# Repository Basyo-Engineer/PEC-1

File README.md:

# PEC-1
Hand made 8bitCPU, Prototype Experimental Computer No.1

## Picture
動いている様子．下記のSample Codeを動かしています．

## CPU Architecture

## Command List
PEC-1で使用可能なコマンド一覧です．

GRx,GRyは汎用レジスタです．ImはImmidiate Data，すなわち即値データです．

## Machine Code
コマンドのマシン語対応表です．

xxやyyは，コマンドで指定したいレジスタ番号の二進数表示です．00(0)～11(3)番まで行けます．

[imdt]は即値データです．データ長は6bitです．

基本的に，オペコード部で各部の制御を行っています．なので，
ジャンプ命令などは仕様上レジスタの指定は冗長と扱うためオペランドはどう書いても問題ありません．
また，即値が「000000」となっているコマンドも，即値の入力は冗長です，

## Sample Code
サンプルコードです．掛け算と引き算を行うプログラムです．

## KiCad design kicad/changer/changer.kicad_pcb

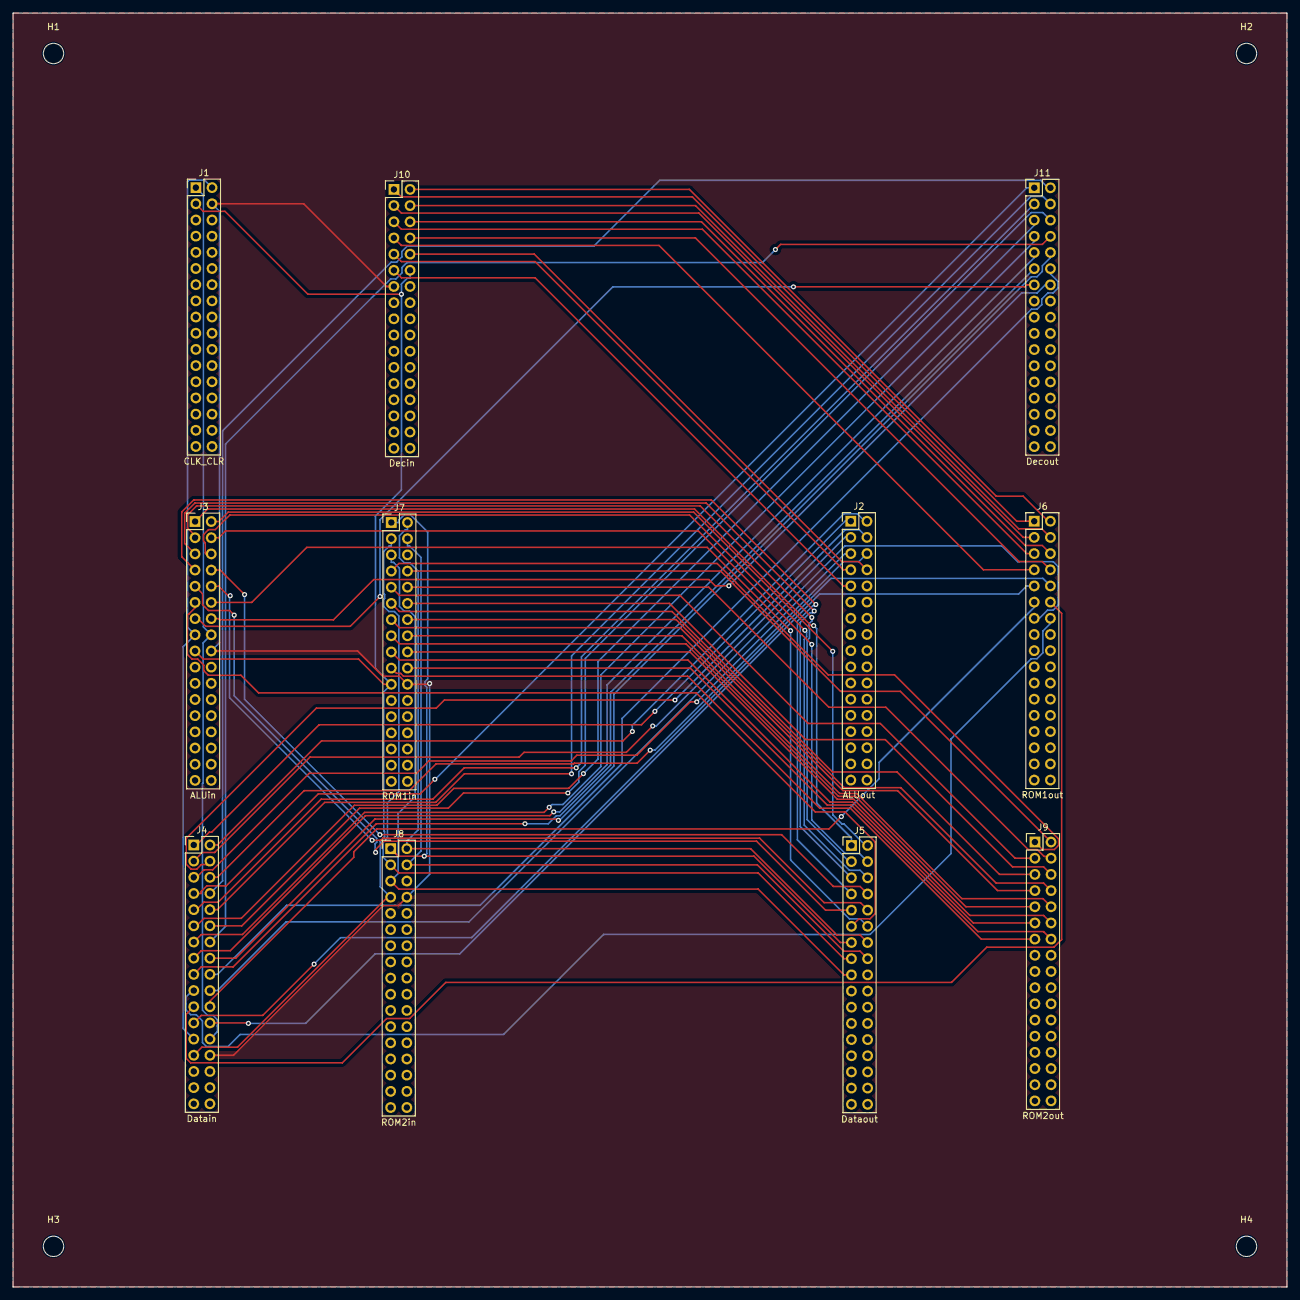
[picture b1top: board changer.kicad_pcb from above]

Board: 2 copper layers, 200.0 x 200.0 mm, 15 parts (0 on the bottom side), 72 nets.

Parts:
H1, H2, H3, H4: MountingHole; MountingHole_3.2mm_M3
J1: CLK_CLR; PinHeader_2x17_P2.54mm_Vertical
J2: ALUout; PinHeader_2x17_P2.54mm_Vertical
J3: ALUin; PinHeader_2x17_P2.54mm_Vertical
J4: Datain; PinHeader_2x17_P2.54mm_Vertical
J5: Dataout; PinHeader_2x17_P2.54mm_Vertical
J6: ROM1out; PinHeader_2x17_P2.54mm_Vertical
J7: ROM1in; PinHeader_2x17_P2.54mm_Vertical
J8: ROM2in; PinHeader_2x17_P2.54mm_Vertical
J9: ROM2out; PinHeader_2x17_P2.54mm_Vertical
J10: Decin; PinHeader_2x17_P2.54mm_Vertical
J11: Decout; PinHeader_2x17_P2.54mm_Vertical

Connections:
2Im0: J7.20, J9.14
2Im1: J7.19, J9.13
2Im2: J7.18, J9.12
2Im3: J7.17, J9.11
2Im4: J7.16, J9.10
2Im5: J7.15, J9.9
2oc0: J7.10, J9.4
2oc1: J7.9, J9.3
2oc2: J7.8, J9.2
2oc3: J7.7, J9.1
2ol0: J7.14, J9.8
2ol1: J7.13, J9.7
2ol2: J7.12, J9.6
2ol3: J7.11, J9.5
+5V: J1.3, J3.17, J4.27, J7.21, J8.7, J10.12
+/-: J3.13, J11.13
A0: J3.1, J5.1
A1: J3.2, J5.2
A2: J3.3, J5.3
A3: J3.4, J5.4
A4: J3.5, J5.5
A5: J3.6, J5.6
A/L: J3.14, J11.14
B0: J3.7, J5.7
B1: J3.8, J5.8
B2: J3.9, J5.9
B3: J3.10, J5.10
B4: J3.11, J5.11
B5: J3.12, J5.12
CLK: J1.1, J3.16, J4.26
CLR: J1.2, J3.15, J4.25
GND: J1.4, J3.18, J4.28, J7.22, J8.8, J10.13
Im0: J4.19, J6.14
Im1: J4.20, J6.13
Im2: J4.21, J6.12
Im3: J4.22, J6.11
Im4: J4.23, J6.10
Im5: J4.24, J6.9
LD0: J4.13, J11.7
LD1: J4.14, J11.8
LD2: J4.15, J11.9
LD3: J4.16, J11.10
LDo: J4.17, J11.11
LDpc: J4.18, J11.12
OFR: J2.8, J10.10
SFR: J2.9, J10.11
Y0: J2.1, J4.1
Y1: J2.2, J4.2
Y2: J2.3, J4.3
Y3: J2.4, J4.4
Y4: J2.5, J4.5
Y5: J2.6, J4.6
ZFR: J2.7, J10.9
oc0: J6.4, J10.4
oc1: J6.3, J10.3
oc2: J6.2, J10.2
oc3: J6.1, J10.1
ol0: J6.8, J10.8
ol1: J6.7, J10.7
ol2: J6.6, J10.6
ol3: J6.5, J10.5
pc0: J5.13, J7.1, J8.1
pc1: J5.14, J7.2, J8.2
pc2: J5.15, J7.3, J8.3
pc3: J5.16, J7.4, J8.4
pc4: J5.17, J7.5, J8.5
sela0: J4.7, J11.1
sela1: J4.8, J11.2
sela2: J4.9, J11.3
selb0: J4.10, J11.4
selb1: J4.11, J11.5
selb2: J4.12, J11.6

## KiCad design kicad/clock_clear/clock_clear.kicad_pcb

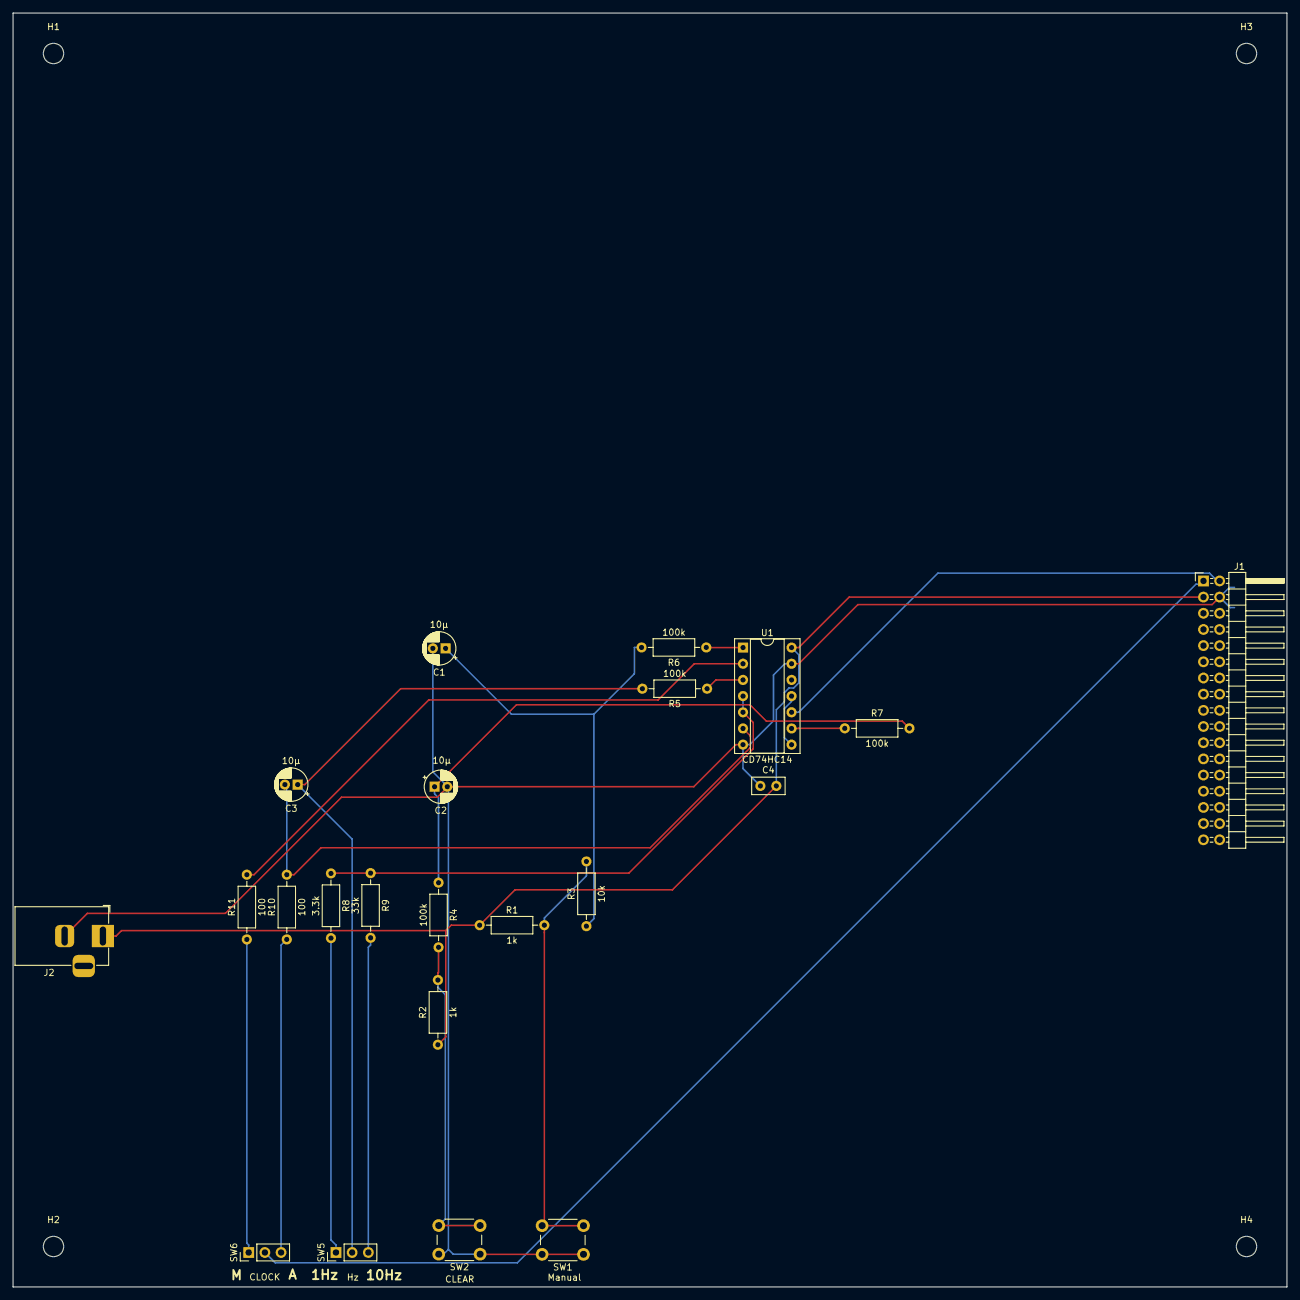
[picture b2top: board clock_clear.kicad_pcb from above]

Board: 2 copper layers, 200.0 x 200.0 mm, 26 parts (0 on the bottom side), 20 nets.

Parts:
C1, C2, C3: 10μ; CP_Radial_D5.0mm_P2.00mm
C4: 0.1μ; C_Disc_D5.0mm_W2.5mm_P2.50mm
H1, H2, H3, H4: MountingHole; MountingHole_3.2mm_M3
J1: Conn_01x34_Pin; PinHeader_2x17_P2.54mm_Horizontal
J2: Barrel_Jack; BarrelJack_Horizontal
R1, R2: 1k; R_Axial_DIN0207_L6.3mm_D2.5mm_P10.16mm_Horizontal
R3: 10k; R_Axial_DIN0207_L6.3mm_D2.5mm_P10.16mm_Horizontal
R4, R5, R6, R7: 100k; R_Axial_DIN0207_L6.3mm_D2.5mm_P10.16mm_Horizontal
R8: 3.3k; R_Axial_DIN0207_L6.3mm_D2.5mm_P10.16mm_Horizontal
R9: 33k; R_Axial_DIN0207_L6.3mm_D2.5mm_P10.16mm_Horizontal
R10, R11: 100; R_Axial_DIN0207_L6.3mm_D2.5mm_P10.16mm_Horizontal
SW1: Manual; SW_PUSH_6mm
SW2: CLEAR; SW_PUSH_6mm
SW5: Hz; PinHeader_1x03_P2.54mm_Vertical
SW6: CLOCK; PinHeader_1x03_P2.54mm_Vertical
U1: CD74HC14; DIP-14_W7.62mm_Socket

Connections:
+5V: C4.2, J1.3, J2.1, R1.1, R2.1, U1.14 (Vcc)
CLK: J1.1, SW6.2 (B)
CLR: J1.2, U1.10
GND: C1.2, C2.2, C4.1, J1.4, J2.2, SW1.1, SW2.1, U1.7 (GND), U1.13
unnamed: C1.1, R3.1, R6.2
unnamed: C2.1, R4.1, R7.2
unnamed: C3.2, R10.2, U1.6
unnamed: R1.2, R3.2, SW1.2
unnamed: R2.2, R4.2, SW2.2
unnamed: R5.1, U1.3
unnamed: R6.1, U1.1
unnamed: R7.1, U1.9
unnamed: R8.1, R9.1, U1.4, U1.5
unnamed: R11.2, U1.2
unnamed: R8.2, SW5.1 (A)
unnamed: C3.1, R5.2, SW5.2 (B)
unnamed: R9.2, SW5.3 (C)
unnamed: R11.1, SW6.1 (A)
unnamed: R10.1, SW6.3 (C)
unnamed: U1.8, U1.11

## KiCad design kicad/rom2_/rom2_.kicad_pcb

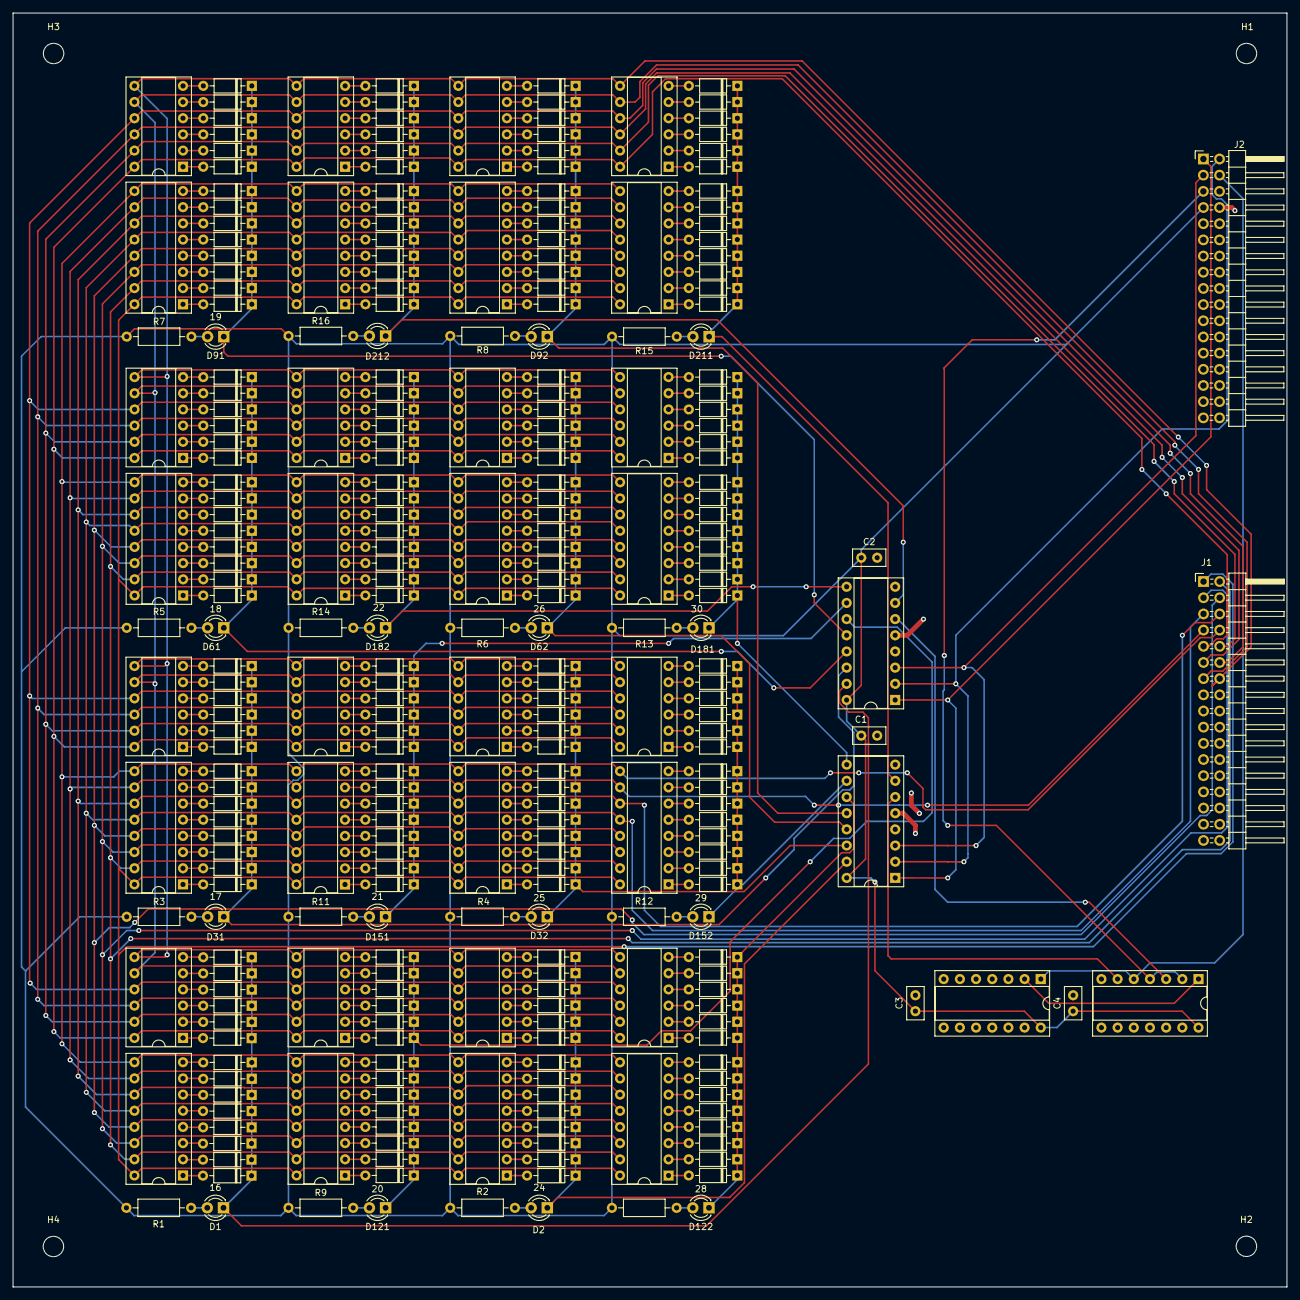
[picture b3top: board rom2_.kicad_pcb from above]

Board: 2 copper layers, 200.0 x 200.0 mm, 302 parts (0 on the bottom side), 280 nets.

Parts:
C1, C2, C3, C4: 0.1μ; C_Disc_D5.0mm_W2.5mm_P2.50mm
D1: 16; LED_D3.0mm
D2: 24; LED_D3.0mm
D3, D4, D5, D6, D7, D8, D9, D10, D11, D12, D13, D14, D15, D16, D17, D18, D19, D20, D21, D22, D23, D24, D25, D26, D27, D28, D29, D30, D33, D34, D35, D36, D37, D38, D39, D40, D41, D42, D43, D44, D45, D46, D47, D48, D49, D50, D51, D52, D53, D54, D55, D56, D57, D58, D59, D60, D63, D64, D65, D66, D67, D68, D69, D70, D71, D72, D73, D74, D75, D76, D77, D78, D79, D80, D81, D82, D83, D84, D85, D86, D87, D88, D89, D90, D93, D94, D95, D96, D97, D98, D99, D100, D101, D102, D103, D104, D105, D106, D107, D108, D109, D110, D111, D112, D113, D114, D115, D116, D117, D118, D119, D120, D123, D124, D125, D126, D127, D128, D129, D130, D131, D132, D133, D134, D135, D136, D137, D138, D139, D140, D141, D142, D143, D144, D145, D146, D147, D148, D149, D150, D153, D154, D155, D156, D157, D158, D159, D160, D161, D162, D163, D164, D165, D166, D167, D168, D169, D170, D171, D172, D173, D174, D175, D176, D177, D178, D179, D180, D183, D184, D185, D186, D187, D188, D189, D190, D191, D192, D193, D194, D195, D196, D197, D198, D199, D200, D201, D202, D203, D204, D205, D206, D207, D208, D209, D210, D213, D214, D215, D216, D217, D218, D219, D220, D221, D222, D223, D224, D225, D226, D227, D228, D229, D230, D231, D232, D233, D234, D235, D236, D237, D238, D239, D240: 1N4148; D_DO-35_SOD27_P7.62mm_Horizontal
D31: 17; LED_D3.0mm
D32: 25; LED_D3.0mm
D61: 18; LED_D3.0mm
D62: 26; LED_D3.0mm
D91: 19; LED_D3.0mm
D92: 27; LED_D3.0mm
D121: 20; LED_D3.0mm
D122: 28; LED_D3.0mm
D151: 21; LED_D3.0mm
D152: 29; LED_D3.0mm
D181: 30; LED_D3.0mm
D182: 22; LED_D3.0mm
D211: 31; LED_D3.0mm
D212: 23; LED_D3.0mm
H1, H2, H3, H4: MountingHole; MountingHole_3.2mm_M3
J1, J2: Conn_01x34_Pin; PinHeader_2x17_P2.54mm_Horizontal
R1, R2, R3, R4, R5, R6, R7, R8, R9, R10, R11, R12, R13, R14, R15, R16: 1K; R_Axial_DIN0207_L6.3mm_D2.5mm_P10.16mm_Horizontal
SW1, SW2, SW5, SW6, SW9, SW10, SW13, SW14, SW17, SW18, SW21, SW22, SW25, SW26, SW29, SW30: SW_DIP_x08; DIP-16_W7.62mm_Socket
SW3, SW4, SW7, SW8, SW11, SW12, SW15, SW16, SW19, SW20, SW23, SW24, SW27, SW28, SW31, SW32: SW_DIP_x06; DIP-12_W7.62mm_Socket
U1: CD74HC14; DIP-14_W7.62mm_Socket
U2: CD74HC08; DIP-14_W7.62mm_Socket
U3, U4: 74HC138; DIP-16_W7.62mm_Socket

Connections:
2Im0: J1.14, SW3.7, SW4.7, SW7.7, SW8.7, SW11.7, SW12.7, SW15.7, SW16.7, SW19.7, SW20.7, SW23.7, SW24.7, SW27.7, SW28.7, SW31.7, SW32.7
2Im1: J1.13, SW3.8, SW4.8, SW7.8, SW8.8, SW11.8, SW12.8, SW15.8, SW16.8, SW19.8, SW20.8, SW23.8, SW24.8, SW27.8, SW28.8, SW31.8, SW32.8
2Im2: J1.12, SW3.9, SW4.9, SW7.9, SW8.9, SW11.9, SW12.9, SW15.9, SW16.9, SW19.9, SW20.9, SW23.9, SW24.9, SW27.9, SW28.9, SW31.9, SW32.9
2Im3: J1.11, SW3.10, SW4.10, SW7.10, SW8.10, SW11.10, SW12.10, SW15.10, SW16.10, SW19.10, SW20.10, SW23.10, SW24.10, SW27.10, SW28.10, SW31.10, SW32.10
2Im4: J1.10, SW3.11, SW4.11, SW7.11, SW8.11, SW11.11, SW12.11, SW15.11, SW16.11, SW19.11, SW20.11, SW23.11, SW24.11, SW27.11, SW28.11, SW31.11, SW32.11
2Im5: J1.9, SW3.12, SW4.12, SW7.12, SW8.12, SW11.12, SW12.12, SW15.12, SW16.12, SW19.12, SW20.12, SW23.12, SW24.12, SW27.12, SW28.12, SW31.12, SW32.12
2oc0: J1.4, SW1.13, SW2.13, SW5.13, SW6.13, SW9.13, SW10.13, SW13.13, SW14.13, SW17.13, SW18.13, SW21.13, SW22.13, SW25.13, SW26.13, SW29.13, SW30.13
2oc1: J1.3, SW1.14, SW2.14, SW5.14, SW6.14, SW9.14, SW10.14, SW13.14, SW14.14, SW17.14, SW18.14, SW21.14, SW22.14, SW25.14, SW26.14, SW29.14, SW30.14
2oc2: J1.2, SW1.15, SW2.15, SW5.15, SW6.15, SW9.15, SW10.15, SW13.15, SW14.15, SW17.15, SW18.15, SW21.15, SW22.15, SW25.15, SW26.15, SW29.15, SW30.15
2oc3: J1.1, SW1.16, SW2.16, SW5.16, SW6.16, SW9.16, SW10.16, SW13.16, SW14.16, SW17.16, SW18.16, SW21.16, SW22.16, SW25.16, SW26.16, SW29.16, SW30.16
2ol0: J1.8, SW1.9, SW2.9, SW5.9, SW6.9, SW9.9, SW10.9, SW13.9, SW14.9, SW17.9, SW18.9, SW21.9, SW22.9, SW25.9, SW26.9, SW29.9, SW30.9
2ol1: J1.7, SW1.10, SW2.10, SW5.10, SW6.10, SW9.10, SW10.10, SW13.10, SW14.10, SW17.10, SW18.10, SW21.10, SW22.10, SW25.10, SW26.10, SW29.10, SW30.10
2ol2: J1.6, SW1.11, SW2.11, SW5.11, SW6.11, SW9.11, SW10.11, SW13.11, SW14.11, SW17.11, SW18.11, SW21.11, SW22.11, SW25.11, SW26.11, SW29.11, SW30.11
2ol3: J1.5, SW1.12, SW2.12, SW5.12, SW6.12, SW9.12, SW10.12, SW13.12, SW14.12, SW17.12, SW18.12, SW21.12, SW22.12, SW25.12, SW26.12, SW29.12, SW30.12
+5V: C1.1, C2.1, C3.1, C4.1, J2.7, R1.1, R2.1, R3.1, R4.1, R5.1, R6.1, R7.1, R8.1, R9.1, R10.1, R11.1, R12.1, R13.1, R14.1, R15.1, R16.1, U1.14 (Vcc), U2.14 (Vcc), U3.16 (VCC), U4.16 (VCC)
GND: C1.2, C2.2, C3.2, C4.2, J2.8, U1.3, U1.5, U1.7 (GND), U1.9, U1.11, U1.13, U2.7 (GND), U2.9, U2.10, U2.12, U2.13, U3.4 (~E0), U3.5 (~E1), U3.8 (GND), U4.4 (~E0), U4.5 (~E1), U4.8 (GND)
unnamed: D1.2 (A), R1.2
unnamed: D1.1 (K), D3.1 (K), D5.1 (K), D7.1 (K), D9.1 (K), D11.1 (K), D13.1 (K), D15.1 (K), D17.1 (K), D19.1 (K), D21.1 (K), D23.1 (K), D25.1 (K), D27.1 (K), D29.1 (K), U3.15 (~Y0)
unnamed: D2.2 (A), R2.2
unnamed: D3.2 (A), SW1.1
unnamed: D4.2 (A), SW2.1
unnamed: D5.2 (A), SW1.2
unnamed: D6.2 (A), SW2.2
unnamed: D7.2 (A), SW1.3
unnamed: D8.2 (A), SW2.3
unnamed: D9.2 (A), SW1.4
unnamed: D10.2 (A), SW2.4
unnamed: D2.1 (K), D4.1 (K), D6.1 (K), D8.1 (K), D10.1 (K), D12.1 (K), D14.1 (K), D16.1 (K), D18.1 (K), D20.1 (K), D22.1 (K), D24.1 (K), D26.1 (K), D28.1 (K), D30.1 (K), U4.15 (~Y0)
unnamed: D11.2 (A), SW1.5
unnamed: D12.2 (A), SW2.5
unnamed: D13.2 (A), SW1.6
unnamed: D14.2 (A), SW2.6
unnamed: D15.2 (A), SW1.7
unnamed: D16.2 (A), SW2.7
unnamed: D17.2 (A), SW1.8
unnamed: D18.2 (A), SW2.8
unnamed: D19.2 (A), SW3.1
unnamed: D20.2 (A), SW4.1
unnamed: D21.2 (A), SW3.2
unnamed: D22.2 (A), SW4.2
unnamed: D23.2 (A), SW3.3
unnamed: D24.2 (A), SW4.3
unnamed: D25.2 (A), SW3.4
unnamed: D26.2 (A), SW4.4
unnamed: D27.2 (A), SW3.5
unnamed: D28.2 (A), SW4.5
unnamed: D29.2 (A), SW3.6
unnamed: D30.2 (A), SW4.6
unnamed: D31.2 (A), R3.2
unnamed: D31.1 (K), D33.1 (K), D35.1 (K), D37.1 (K), D39.1 (K), D41.1 (K), D43.1 (K), D45.1 (K), D47.1 (K), D49.1 (K), D51.1 (K), D53.1 (K), D55.1 (K), D57.1 (K), D59.1 (K), U3.14 (~Y1)
unnamed: D32.2 (A), R4.2
unnamed: D32.1 (K), D34.1 (K), D36.1 (K), D38.1 (K), D40.1 (K), D42.1 (K), D44.1 (K), D46.1 (K), D48.1 (K), D50.1 (K), D52.1 (K), D54.1 (K), D56.1 (K), D58.1 (K), D60.1 (K), U4.14 (~Y1)
unnamed: D33.2 (A), SW5.1
unnamed: D34.2 (A), SW6.1
unnamed: D35.2 (A), SW5.2
unnamed: D36.2 (A), SW6.2
unnamed: D37.2 (A), SW5.3
unnamed: D38.2 (A), SW6.3
unnamed: D39.2 (A), SW5.4
unnamed: D40.2 (A), SW6.4
unnamed: D41.2 (A), SW5.5
unnamed: D42.2 (A), SW6.5
unnamed: D43.2 (A), SW5.6
unnamed: D44.2 (A), SW6.6
unnamed: D45.2 (A), SW5.7
unnamed: D46.2 (A), SW6.7
unnamed: D47.2 (A), SW5.8
unnamed: D48.2 (A), SW6.8
unnamed: D49.2 (A), SW7.1
unnamed: D50.2 (A), SW8.1
unnamed: D51.2 (A), SW7.2
unnamed: D52.2 (A), SW8.2
unnamed: D53.2 (A), SW7.3
unnamed: D54.2 (A), SW8.3
unnamed: D55.2 (A), SW7.4
unnamed: D56.2 (A), SW8.4
unnamed: D57.2 (A), SW7.5
unnamed: D58.2 (A), SW8.5
unnamed: D59.2 (A), SW7.6
unnamed: D60.2 (A), SW8.6
unnamed: D61.2 (A), R5.2
unnamed: D61.1 (K), D63.1 (K), D65.1 (K), D67.1 (K), D69.1 (K), D71.1 (K), D73.1 (K), D75.1 (K), D77.1 (K), D79.1 (K), D81.1 (K), D83.1 (K), D85.1 (K), D87.1 (K), D89.1 (K), U3.13 (~Y2)
unnamed: D62.2 (A), R6.2
unnamed: D62.1 (K), D64.1 (K), D66.1 (K), D68.1 (K), D70.1 (K), D72.1 (K), D74.1 (K), D76.1 (K), D78.1 (K), D80.1 (K), D82.1 (K), D84.1 (K), D86.1 (K), D88.1 (K), D90.1 (K), U4.13 (~Y2)
unnamed: D63.2 (A), SW9.1
unnamed: D64.2 (A), SW10.1
unnamed: D65.2 (A), SW9.2
unnamed: D66.2 (A), SW10.2
unnamed: D67.2 (A), SW9.3
unnamed: D68.2 (A), SW10.3
unnamed: D69.2 (A), SW9.4
unnamed: D70.2 (A), SW10.4
unnamed: D71.2 (A), SW9.5
unnamed: D72.2 (A), SW10.5
unnamed: D73.2 (A), SW9.6
unnamed: D74.2 (A), SW10.6
unnamed: D75.2 (A), SW9.7
unnamed: D76.2 (A), SW10.7
unnamed: D77.2 (A), SW9.8
unnamed: D78.2 (A), SW10.8
unnamed: D79.2 (A), SW11.1
unnamed: D80.2 (A), SW12.1
unnamed: D81.2 (A), SW11.2
unnamed: D82.2 (A), SW12.2
unnamed: D83.2 (A), SW11.3
unnamed: D84.2 (A), SW12.3
unnamed: D85.2 (A), SW11.4
unnamed: D86.2 (A), SW12.4
unnamed: D87.2 (A), SW11.5
unnamed: D88.2 (A), SW12.5
unnamed: D89.2 (A), SW11.6
unnamed: D90.2 (A), SW12.6
unnamed: D91.2 (A), R7.2
unnamed: D92.2 (A), R8.2
unnamed: D93.2 (A), SW13.1
unnamed: D94.2 (A), SW14.1
unnamed: D95.2 (A), SW13.2
unnamed: D96.2 (A), SW14.2
unnamed: D97.2 (A), SW13.3
unnamed: D98.2 (A), SW14.3
unnamed: D99.2 (A), SW13.4
unnamed: D100.2 (A), SW14.4
unnamed: D92.1 (K), D94.1 (K), D96.1 (K), D98.1 (K), D100.1 (K), D102.1 (K), D104.1 (K), D106.1 (K), D108.1 (K), D110.1 (K), D112.1 (K), D114.1 (K), D116.1 (K), D118.1 (K), D120.1 (K), U4.12 (~Y3)
unnamed: D101.2 (A), SW13.5
unnamed: D91.1 (K), D93.1 (K), D95.1 (K), D97.1 (K), D99.1 (K), D101.1 (K), D103.1 (K), D105.1 (K), D107.1 (K), D109.1 (K), D111.1 (K), D113.1 (K), D115.1 (K), D117.1 (K), D119.1 (K), U3.12 (~Y3)
unnamed: D102.2 (A), SW14.5
unnamed: D103.2 (A), SW13.6
unnamed: D104.2 (A), SW14.6
unnamed: D105.2 (A), SW13.7
unnamed: D106.2 (A), SW14.7
unnamed: D107.2 (A), SW13.8
unnamed: D108.2 (A), SW14.8
unnamed: D109.2 (A), SW15.1
unnamed: D110.2 (A), SW16.1
unnamed: D111.2 (A), SW15.2
unnamed: D112.2 (A), SW16.2
unnamed: D113.2 (A), SW15.3
unnamed: D114.2 (A), SW16.3
unnamed: D115.2 (A), SW15.4
unnamed: D116.2 (A), SW16.4
unnamed: D117.2 (A), SW15.5
unnamed: D118.2 (A), SW16.5
unnamed: D119.2 (A), SW15.6
unnamed: D120.2 (A), SW16.6
unnamed: D121.2 (A), R9.2
unnamed: D121.1 (K), D123.1 (K), D125.1 (K), D127.1 (K), D129.1 (K), D131.1 (K), D133.1 (K), D135.1 (K), D137.1 (K), D139.1 (K), D141.1 (K), D143.1 (K), D145.1 (K), D147.1 (K), D149.1 (K), U3.11 (~Y4)
unnamed: D122.2 (A), R10.2
unnamed: D122.1 (K), D124.1 (K), D126.1 (K), D128.1 (K), D130.1 (K), D132.1 (K), D134.1 (K), D136.1 (K), D138.1 (K), D140.1 (K), D142.1 (K), D144.1 (K), D146.1 (K), D148.1 (K), D150.1 (K), U4.11 (~Y4)
unnamed: D123.2 (A), SW17.1
unnamed: D124.2 (A), SW18.1
unnamed: D125.2 (A), SW17.2
unnamed: D126.2 (A), SW18.2
unnamed: D127.2 (A), SW17.3
unnamed: D128.2 (A), SW18.3
unnamed: D129.2 (A), SW17.4
unnamed: D130.2 (A), SW18.4
unnamed: D131.2 (A), SW17.5
unnamed: D132.2 (A), SW18.5
unnamed: D133.2 (A), SW17.6
unnamed: D134.2 (A), SW18.6
unnamed: D135.2 (A), SW17.7
unnamed: D136.2 (A), SW18.7
unnamed: D137.2 (A), SW17.8
unnamed: D138.2 (A), SW18.8
unnamed: D139.2 (A), SW19.1
unnamed: D140.2 (A), SW20.1
unnamed: D141.2 (A), SW19.2
unnamed: D142.2 (A), SW20.2
unnamed: D143.2 (A), SW19.3
unnamed: D144.2 (A), SW20.3
unnamed: D145.2 (A), SW19.4
unnamed: D146.2 (A), SW20.4
unnamed: D147.2 (A), SW19.5
unnamed: D148.2 (A), SW20.5
unnamed: D149.2 (A), SW19.6
unnamed: D150.2 (A), SW20.6
unnamed: D151.2 (A), R11.2
unnamed: D151.1 (K), D153.1 (K), D155.1 (K), D157.1 (K), D159.1 (K), D161.1 (K), D163.1 (K), D165.1 (K), D167.1 (K), D169.1 (K), D171.1 (K), D173.1 (K), D175.1 (K), D177.1 (K), D179.1 (K), U3.10 (~Y5)
unnamed: D152.2 (A), R12.2
unnamed: D152.1 (K), D154.1 (K), D156.1 (K), D158.1 (K), D160.1 (K), D162.1 (K), D164.1 (K), D166.1 (K), D168.1 (K), D170.1 (K), D172.1 (K), D174.1 (K), D176.1 (K), D178.1 (K), D180.1 (K), U4.10 (~Y5)
unnamed: D153.2 (A), SW21.1
unnamed: D154.2 (A), SW22.1
unnamed: D155.2 (A), SW21.2
unnamed: D156.2 (A), SW22.2
unnamed: D157.2 (A), SW21.3
unnamed: D158.2 (A), SW22.3
unnamed: D159.2 (A), SW21.4
unnamed: D160.2 (A), SW22.4
unnamed: D161.2 (A), SW21.5
unnamed: D162.2 (A), SW22.5
unnamed: D163.2 (A), SW21.6
unnamed: D164.2 (A), SW22.6
unnamed: D165.2 (A), SW21.7
unnamed: D166.2 (A), SW22.7
unnamed: D167.2 (A), SW21.8
unnamed: D168.2 (A), SW22.8
unnamed: D169.2 (A), SW23.1
unnamed: D170.2 (A), SW24.1
unnamed: D171.2 (A), SW23.2
unnamed: D172.2 (A), SW24.2
unnamed: D173.2 (A), SW23.3
unnamed: D174.2 (A), SW24.3
unnamed: D175.2 (A), SW23.4
unnamed: D176.2 (A), SW24.4
unnamed: D177.2 (A), SW23.5
unnamed: D178.2 (A), SW24.5
unnamed: D179.2 (A), SW23.6
unnamed: D180.2 (A), SW24.6
unnamed: D181.2 (A), R13.2
unnamed: D181.1 (K), D183.1 (K), D185.1 (K), D187.1 (K), D189.1 (K), D191.1 (K), D193.1 (K), D195.1 (K), D197.1 (K), D199.1 (K), D201.1 (K), D203.1 (K), D205.1 (K), D207.1 (K), D209.1 (K), U4.9 (~Y6)
unnamed: D182.2 (A), R14.2
unnamed: D182.1 (K), D184.1 (K), D186.1 (K), D188.1 (K), D190.1 (K), D192.1 (K), D194.1 (K), D196.1 (K), D198.1 (K), D200.1 (K), D202.1 (K), D204.1 (K), D206.1 (K), D208.1 (K), D210.1 (K), U3.9 (~Y6)
unnamed: D183.2 (A), SW25.1
unnamed: D184.2 (A), SW26.1
unnamed: D185.2 (A), SW25.2
unnamed: D186.2 (A), SW26.2
unnamed: D187.2 (A), SW25.3
unnamed: D188.2 (A), SW26.3
unnamed: D189.2 (A), SW25.4
unnamed: D190.2 (A), SW26.4
unnamed: D191.2 (A), SW25.5
unnamed: D192.2 (A), SW26.5
unnamed: D193.2 (A), SW25.6
unnamed: D194.2 (A), SW26.6
unnamed: D195.2 (A), SW25.7
unnamed: D196.2 (A), SW26.7
unnamed: D197.2 (A), SW25.8
unnamed: D198.2 (A), SW26.8
unnamed: D199.2 (A), SW27.1
unnamed: D200.2 (A), SW28.1
unnamed: D201.2 (A), SW27.2
unnamed: D202.2 (A), SW28.2
unnamed: D203.2 (A), SW27.3
unnamed: D204.2 (A), SW28.3
unnamed: D205.2 (A), SW27.4
unnamed: D206.2 (A), SW28.4
unnamed: D207.2 (A), SW27.5
unnamed: D208.2 (A), SW28.5
unnamed: D209.2 (A), SW27.6
unnamed: D210.2 (A), SW28.6
unnamed: D211.2 (A), R15.2
unnamed: D211.1 (K), D213.1 (K), D215.1 (K), D217.1 (K), D219.1 (K), D221.1 (K), D223.1 (K), D225.1 (K), D227.1 (K), D229.1 (K), D231.1 (K), D233.1 (K), D235.1 (K), D237.1 (K), D239.1 (K), U4.7 (~Y7)
unnamed: D212.2 (A), R16.2
unnamed: D212.1 (K), D214.1 (K), D216.1 (K), D218.1 (K), D220.1 (K), D222.1 (K), D224.1 (K), D226.1 (K), D228.1 (K), D230.1 (K), D232.1 (K), D234.1 (K), D236.1 (K), D238.1 (K), D240.1 (K), U3.7 (~Y7)
unnamed: D213.2 (A), SW29.1
unnamed: D214.2 (A), SW30.1
unnamed: D215.2 (A), SW29.2
unnamed: D216.2 (A), SW30.2
unnamed: D217.2 (A), SW29.3
unnamed: D218.2 (A), SW30.3
unnamed: D219.2 (A), SW29.4
unnamed: D220.2 (A), SW30.4
unnamed: D221.2 (A), SW29.5
unnamed: D222.2 (A), SW30.5
unnamed: D223.2 (A), SW29.6
unnamed: D224.2 (A), SW30.6
unnamed: D225.2 (A), SW29.7
unnamed: D226.2 (A), SW30.7
unnamed: D227.2 (A), SW29.8
unnamed: D228.2 (A), SW30.8
unnamed: D229.2 (A), SW31.1
unnamed: D230.2 (A), SW32.1
unnamed: D231.2 (A), SW31.2
unnamed: D232.2 (A), SW32.2
unnamed: D233.2 (A), SW31.3
unnamed: D234.2 (A), SW32.3
unnamed: D235.2 (A), SW31.4
unnamed: D236.2 (A), SW32.4
unnamed: D237.2 (A), SW31.5
unnamed: D238.2 (A), SW32.5
unnamed: D239.2 (A), SW31.6
unnamed: D240.2 (A), SW32.6
unnamed: U1.2, U2.1
unnamed: U2.3, U3.6 (E2)
unnamed: U2.6, U4.6 (E2)
pc0: J2.1, U3.1 (A0), U4.1 (A0)
pc1: J2.2, U3.2 (A1), U4.2 (A1)
pc2: J2.3, U3.3 (A2), U4.3 (A2)
pc3: J2.4, U1.1, U2.5
pc4: J2.5, U2.2, U2.4
